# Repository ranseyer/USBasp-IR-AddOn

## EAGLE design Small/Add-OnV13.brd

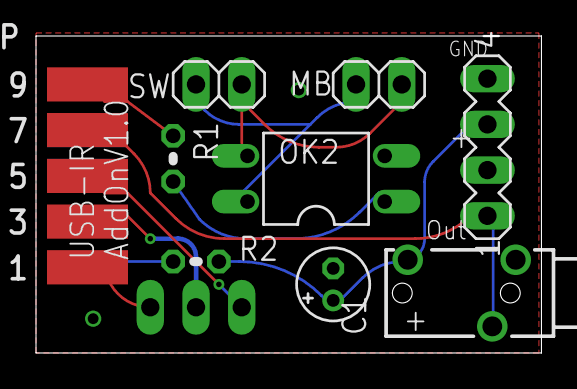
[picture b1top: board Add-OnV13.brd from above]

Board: 2 copper layers, 28.1 x 17.6 mm, 10 parts (1 on the bottom side), 11 nets.

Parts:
2USB-ASP: CON2X5EDGE
C1: 4,7uF; E1,8-4
FREI: MA03-1
MB: 1X02
OK2: PC817; DIL04
R1: 100; 0204V
R2: 560; 0204V
SV1: MA04-1
SW: 1X02
X1: 1501_03

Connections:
GND: 2USB-ASP.P$4, 2USB-ASP.P$6, 2USB-ASP.P$8, 2USB-ASP.P$10, C1.-, OK2.2, SV1.4, X1.1
MISO: 2USB-ASP.P$9, R1.1
MOSI: 2USB-ASP.P$1, FREI.3
unnamed: C1.+, R2.1, SV1.3, X1.3
unnamed: OK2.1, R1.2
unnamed: MB.2, OK2.4, SW.1
unnamed: MB.1, OK2.3, SW.2
NC: 2USB-ASP.P$3, FREI.2
RST: 2USB-ASP.P$5, FREI.1
SCK: 2USB-ASP.P$7, SV1.1, X1.2
VCC: 2USB-ASP.P$2, R2.2
